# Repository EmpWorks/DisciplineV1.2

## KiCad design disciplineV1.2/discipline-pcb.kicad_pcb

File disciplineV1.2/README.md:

# DISCIPLINE V1.5
Originally created by coseyfannitutti 

**65% keyboard assembled with only through hole components, including usb type-c**

### Disclaimer
This board is a heavily-modified coseyfannitutti DISCIPLINE V1 Pcb While the schematic, basic layout etc is essentially the same, it supports additional features like Hot-swap,Encoder etc.

Key differences:
- supports hotswap PCB sockets
- added WS2812B Led strip footprint for backlit 
- Optional encoder support

Disclaimer: Use these files at your own risk.

## Assembly
For the components required, you may refer to the bill of materials here [BOM](https://octopart.com/bom-tool/W4rybyut).

All the components can be soldered using a regular soldering iron.

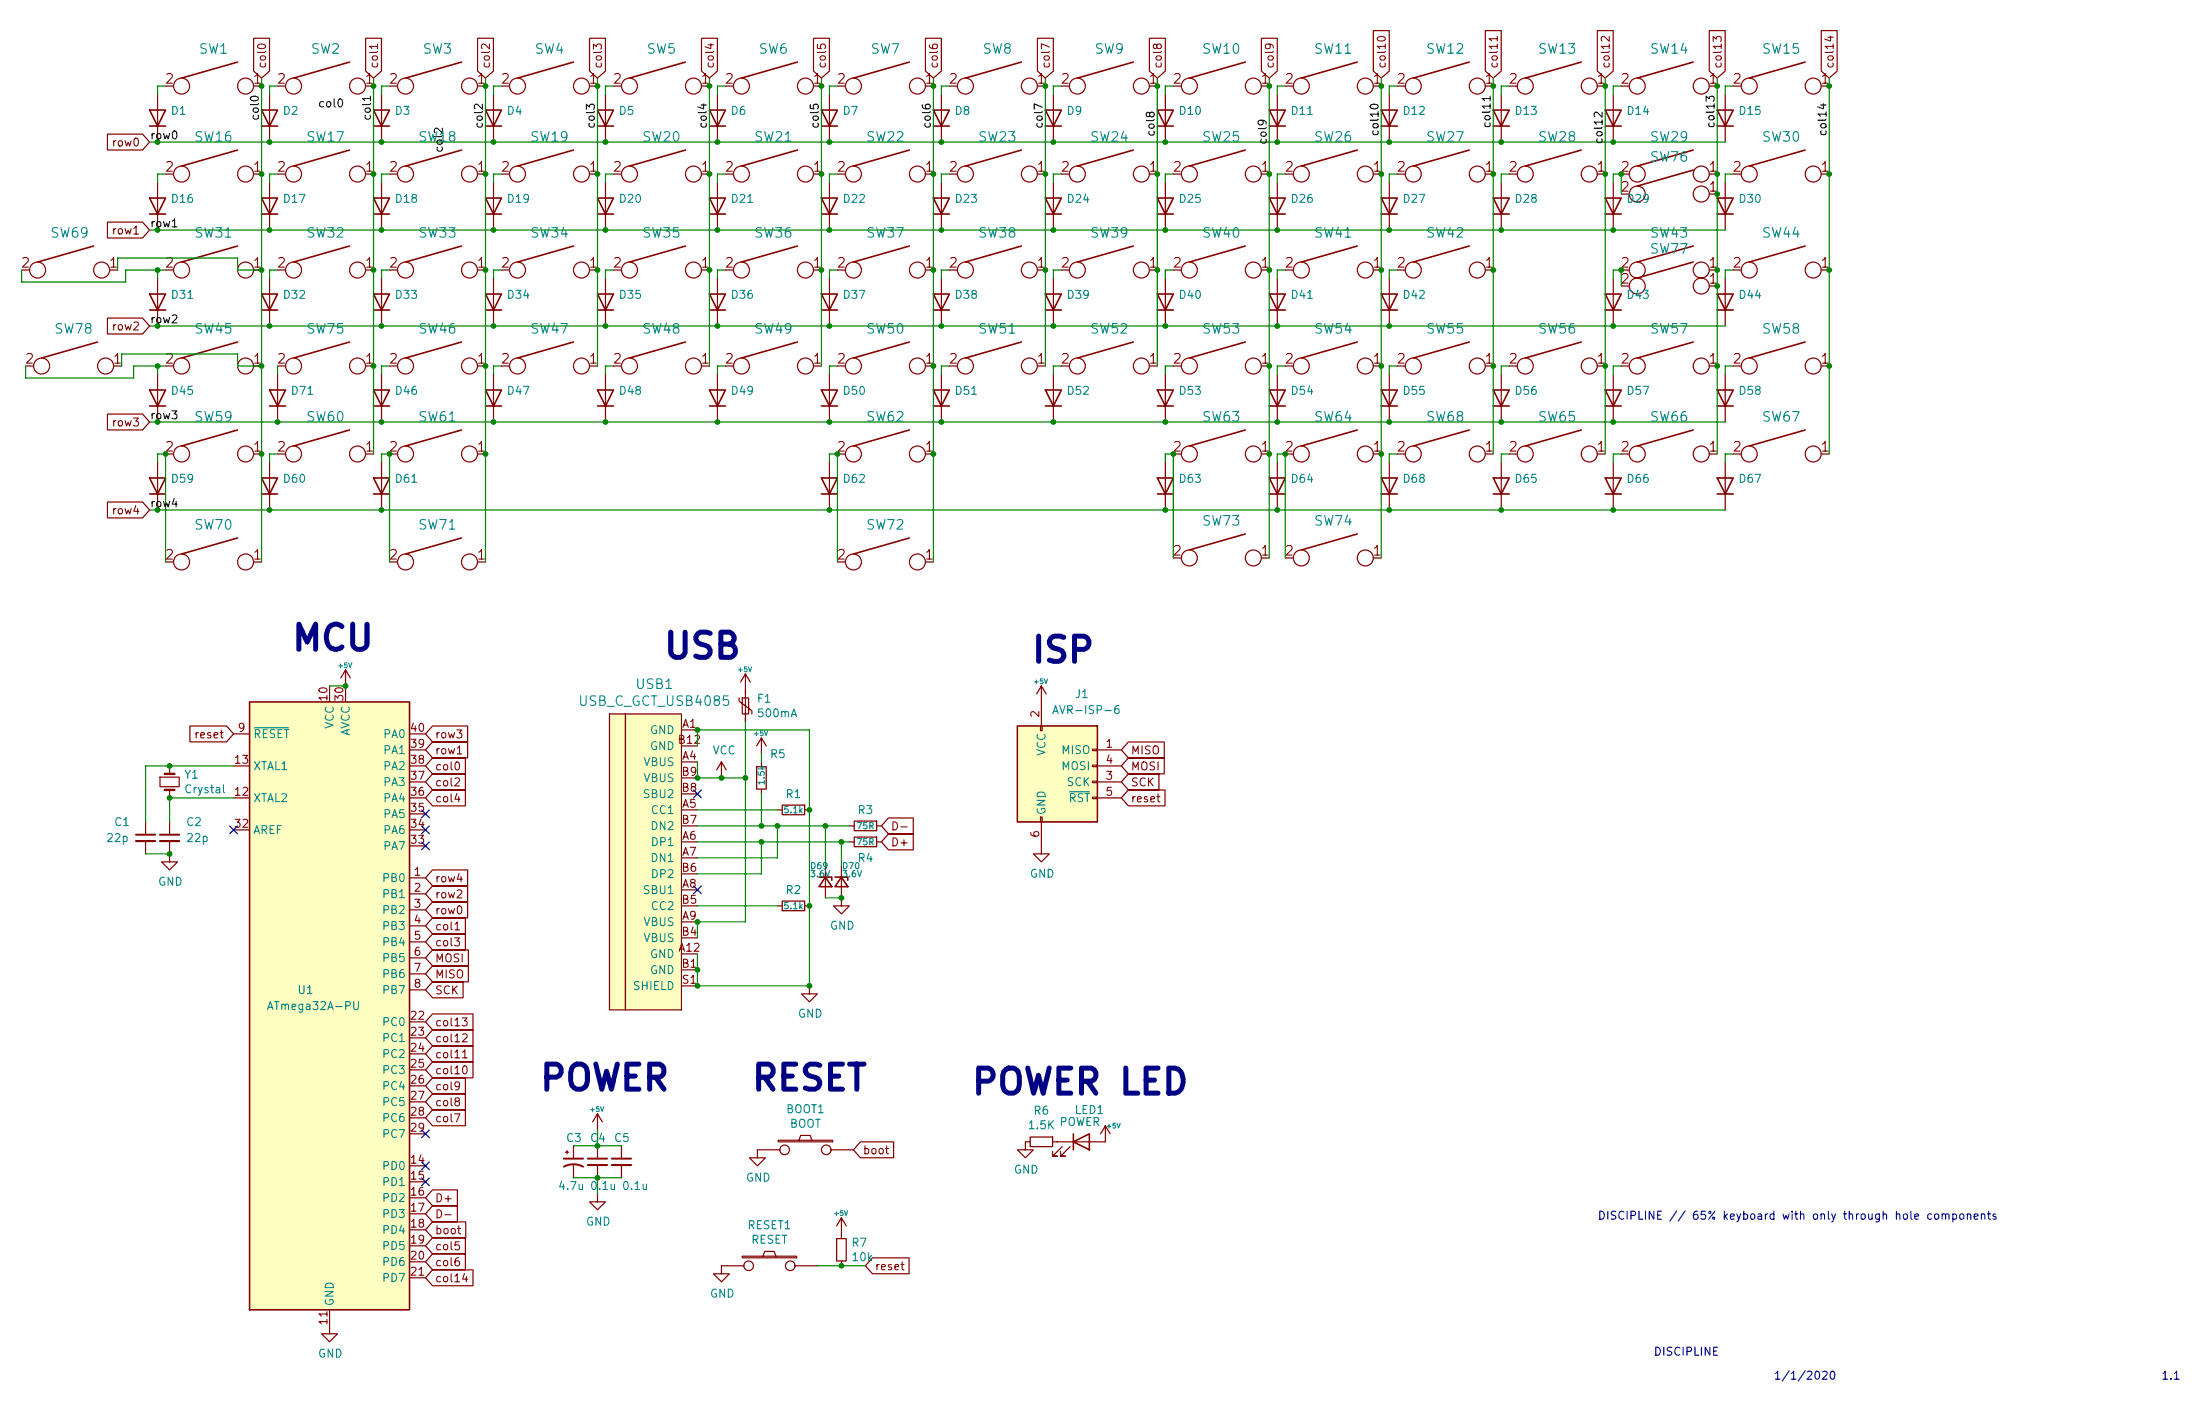
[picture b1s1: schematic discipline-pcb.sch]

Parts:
BOOT1: BOOT; SW_PUSH_6mm
C1, C2: 22p; C_Disc_D3.0mm_W1.6mm_P2.50mm
C3: 4.7u; CP_Radial_D4.0mm_P1.50mm
C4, C5: 0.1u; C_Disc_D4.3mm_W1.9mm_P5.00mm
D1, D2, D3, D4, D5, D6, D7, D8, D9, D10, D11, D12, D13, D14, D15, D16, D17, D18, D19, D20, D21, D22, D23, D24, D25, D26, D27, D28, D29, D30, D31, D32, D33, D34, D35, D36, D37, D38, D39, D40, D41, D42, D43, D44, D45, D46, D47, D48, D49, D50, D51, D52, D53, D54, D55, D56, D57, D58, D59, D60, D61, D62, D63, D64, D65, D66, D67, D68, D71: D_DO-35_SOD27_P5.08mm_Horizontal
D69, D70: 3.6V; D_DO-35_SOD27_P5.08mm_Horizontal
F1: 500mA; polyfuse_5.1mm
J1: AVR-ISP-6; AVR_ICSP_3x2
LED1: POWER; LED_D3.0mm
R1, R2: 5.1k; R_Axial_DIN0204_L3.6mm_D1.6mm_P5.08mm_Horizontal
R3, R4: 75R; R_Axial_DIN0204_L3.6mm_D1.6mm_P5.08mm_Horizontal
R5: 1.5k; R_Axial_DIN0204_L3.6mm_D1.6mm_P5.08mm_Horizontal
R6: 1.5K; R_Axial_DIN0204_L3.6mm_D1.6mm_P5.08mm_Horizontal
R7: 10k; R_Axial_DIN0204_L3.6mm_D1.6mm_P5.08mm_Horizontal
RESET1: RESET; SW_PUSH_6mm
SW1, SW2, SW3, SW4, SW5, SW6, SW7, SW8, SW9, SW10, SW11, SW12, SW13, SW15, SW17, SW18, SW19, SW20, SW21, SW22, SW23, SW24, SW25, SW26, SW27, SW28, SW30, SW32, SW33, SW34, SW35, SW36, SW37, SW38, SW39, SW40, SW41, SW42, SW44, SW46, SW47, SW48, SW49, SW50, SW51, SW52, SW53, SW54, SW55, SW57, SW58, SW62, SW65, SW66, SW67, SW68, SW72, SW75: KEYSW; MXOnly-1U-Hotswap
SW14: KEYSW; MXOnly-2U-Hotswap
SW16, SW29, SW70, SW71, SW73, SW74: KEYSW; MXOnly-1.5U-Hotswap
SW31, SW56: KEYSW; MXOnly-1.75U-Hotswap
SW43, SW45: KEYSW; MXOnly-2.25U-Hotswap
SW59, SW60, SW61, SW63, SW64, SW69: KEYSW; MXOnly-1.25U-Hotswap
SW76: KEYSW; SW_Cherry_MX1A_ISOEnter_PCB_ReversedStabilizer
SW77: KEYSW; SW_Cherry_MX1A_1.00u_PCB-NOSCREEN
SW78: KEYSW; SW_Cherry_MX1A_1.25u_PCBNOSCREEN
U1: ATmega32A-PU; DIP-40_W15.24mm
USB1: USB_C_GCT_USB4085
Y1: Crystal; Crystal_HC49-4H_Vertical

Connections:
+5V: C3.1, C4.1, C5.1, F1.1, J1.2 (VCC), LED1.2 (A), R5.1, R7.1, U1.10 (VCC), U1.30 (AVCC); also elsewhere on the board
D+: R4.1, U1.16 (PD2)
D-: R3.1, U1.17 (PD3)
GND: BOOT1.1, C1.2, C2.2, C3.2, C4.2, C5.2, D69.2 (A), D70.2 (A), J1.6 (GND), R1.1, R2.2, R6.2, RESET1.1, U1.11 (GND), U1.31 (GND), USB1.A1 (GND), USB1.A12 (GND), USB1.B1 (GND), USB1.B12 (GND), USB1.S1 (SHIELD); also elsewhere on the board
MISO: J1.1 (MISO), U1.7 (PB6)
MOSI: J1.4 (MOSI), U1.6 (PB5)
unnamed: C1.1, U1.13 (XTAL1), Y1.1
unnamed: C2.1, U1.12 (XTAL2), Y1.2
unnamed: D1.2 (A), SW1.2
unnamed: D2.2 (A), SW2.2
unnamed: D3.2 (A), SW3.2
unnamed: D4.2 (A), SW4.2
unnamed: D5.2 (A), SW5.2
unnamed: D6.2 (A), SW6.2
unnamed: D7.2 (A), SW7.2
unnamed: D8.2 (A), SW8.2
unnamed: D9.2 (A), SW9.2
unnamed: D10.2 (A), SW10.2
unnamed: D11.2 (A), SW11.2
unnamed: D12.2 (A), SW12.2
unnamed: D13.2 (A), SW13.2
unnamed: D14.2 (A), SW14.2
unnamed 22: D15.2 (A), SW15.2; also elsewhere on the board
unnamed: D16.2 (A), SW16.2
unnamed: D17.2 (A), SW17.2
unnamed: D18.2 (A), SW18.2
unnamed: D19.2 (A), SW19.2
unnamed: D20.2 (A), SW20.2
unnamed: D21.2 (A), SW21.2
unnamed: D22.2 (A), SW22.2
unnamed: D23.2 (A), SW23.2
unnamed: D24.2 (A), SW24.2
unnamed: D25.2 (A), SW25.2
unnamed: D26.2 (A), SW26.2
unnamed: D27.2 (A), SW27.2
unnamed: D28.2 (A), SW28.2
unnamed: D29.2 (A), SW29.2, SW76.2
unnamed: D30.2 (A), SW30.2
unnamed: D31.2 (A), SW31.2, SW69.2
unnamed: D32.2 (A), SW32.2
unnamed: D33.2 (A), SW33.2
unnamed: D34.2 (A), SW34.2
unnamed: D35.2 (A), SW35.2
unnamed: D36.2 (A), SW36.2
unnamed: D37.2 (A), SW37.2
unnamed: D38.2 (A), SW38.2
unnamed: D39.2 (A), SW39.2
unnamed: D40.2 (A), SW40.2
unnamed: D41.2 (A), SW41.2
unnamed: D42.2 (A), SW42.2
unnamed: D43.2 (A), SW43.2, SW77.2
unnamed: D44.2 (A), SW44.2
unnamed: D45.2 (A), SW45.2, SW78.2
unnamed: D46.2 (A), SW46.2
unnamed: D47.2 (A), SW47.2
unnamed: D48.2 (A), SW48.2
unnamed: D49.2 (A), SW49.2
unnamed: D50.2 (A), SW50.2
unnamed: D51.2 (A), SW51.2
unnamed: D52.2 (A), SW52.2
unnamed: D53.2 (A), SW53.2
unnamed: D54.2 (A), SW54.2
unnamed: D55.2 (A), SW55.2
unnamed: D56.2 (A), SW56.2
unnamed: D57.2 (A), SW57.2
unnamed: D58.2 (A), SW58.2
unnamed: D59.2 (A), SW59.2, SW70.2
unnamed: D60.2 (A), SW60.2
unnamed: D61.2 (A), SW61.2, SW71.2
unnamed: D62.2 (A), SW62.2, SW72.2
unnamed: D63.2 (A), SW63.2, SW73.2
unnamed: D64.2 (A), SW64.2, SW74.2
unnamed: D65.2 (A), SW65.2
unnamed: D66.2 (A), SW66.2
unnamed: D67.2 (A), SW67.2
unnamed: D68.2 (A), SW68.2
unnamed: D69.1 (K), R3.2, R5.2, USB1.A7 (DN1), USB1.B7 (DN2)
unnamed: D70.1 (K), R4.2, USB1.A6 (DP1), USB1.B6 (DP2)
unnamed: D71.2 (A), SW75.2
unnamed: LED1.1 (K), R6.1
unnamed: R1.2, USB1.A5 (CC1)
unnamed: R2.1, USB1.B5 (CC2)
SCK: J1.3 (SCK), U1.8 (PB7)
VCC: F1.2, USB1.A4 (VBUS), USB1.A9 (VBUS), USB1.B4 (VBUS), USB1.B9 (VBUS)
a: U1.14 (PD0); also elsewhere on the board
b: U1.15 (PD1); also elsewhere on the board
boot: BOOT1.2, U1.18 (PD4)
col0: SW1.1, SW16.1, SW31.1, SW45.1, SW59.1, SW69.1, SW70.1, SW78.1, U1.38 (PA2)
col1: SW2.1, SW17.1, SW32.1, SW60.1, SW75.1, U1.4 (PB3)
col2: SW3.1, SW18.1, SW33.1, SW46.1, SW61.1, SW71.1, U1.37 (PA3)
col3: SW4.1, SW19.1, SW34.1, SW47.1, U1.5 (PB4)
col4: SW5.1, SW20.1, SW35.1, SW48.1, U1.36 (PA4)
col5: SW6.1, SW21.1, SW36.1, SW49.1, U1.19 (PD5)
col6: SW7.1, SW22.1, SW37.1, SW50.1, SW62.1, SW72.1, U1.20 (PD6)
col7: SW8.1, SW23.1, SW38.1, SW51.1, U1.28 (PC6)
col8: SW9.1, SW24.1, SW39.1, SW52.1, U1.27 (PC5)
col9: SW10.1, SW25.1, SW40.1, SW53.1, SW63.1, SW73.1, U1.26 (PC4)
col10: SW11.1, SW26.1, SW41.1, SW54.1, SW64.1, SW74.1, U1.25 (PC3)
col11: SW12.1, SW27.1, SW42.1, SW55.1, SW68.1, U1.24 (PC2)
col12: SW13.1, SW28.1, SW56.1, SW65.1, U1.23 (PC1)
col13: SW14.1, SW29.1, SW43.1, SW57.1, SW66.1, SW76.1, SW77.1, U1.22 (PC0)
col14: SW15.1, SW30.1, SW44.1, SW58.1, SW67.1, U1.21 (PD7); also elsewhere on the board
led: U1.29 (PC7); also elsewhere on the board
reset: J1.5 (~RST), R7.2, RESET1.2, U1.9 (~RESET)
row0: D1.1 (K), D2.1 (K), D3.1 (K), D4.1 (K), D5.1 (K), D6.1 (K), D7.1 (K), D8.1 (K), D9.1 (K), D10.1 (K), D11.1 (K), D12.1 (K), D13.1 (K), D14.1 (K), D15.1 (K), U1.3 (PB2)
row1: D16.1 (K), D17.1 (K), D18.1 (K), D19.1 (K), D20.1 (K), D21.1 (K), D22.1 (K), D23.1 (K), D24.1 (K), D25.1 (K), D26.1 (K), D27.1 (K), D28.1 (K), D29.1 (K), D30.1 (K), U1.39 (PA1)
row2: D31.1 (K), D32.1 (K), D33.1 (K), D34.1 (K), D35.1 (K), D36.1 (K), D37.1 (K), D38.1 (K), D39.1 (K), D40.1 (K), D41.1 (K), D42.1 (K), D43.1 (K), D44.1 (K), U1.2 (PB1)
row3: D45.1 (K), D46.1 (K), D47.1 (K), D48.1 (K), D49.1 (K), D50.1 (K), D51.1 (K), D52.1 (K), D53.1 (K), D54.1 (K), D55.1 (K), D56.1 (K), D57.1 (K), D58.1 (K), D71.1 (K), U1.40 (PA0)
row4: D59.1 (K), D60.1 (K), D61.1 (K), D62.1 (K), D63.1 (K), D64.1 (K), D65.1 (K), D66.1 (K), D67.1 (K), D68.1 (K), U1.1 (PB0)

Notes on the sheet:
DISCIPLINE // 65% keyboard with only through hole components
1/1/2020
DISCIPLINE
1.1
MCU
USB
ISP
POWER
RESET
POWER LED

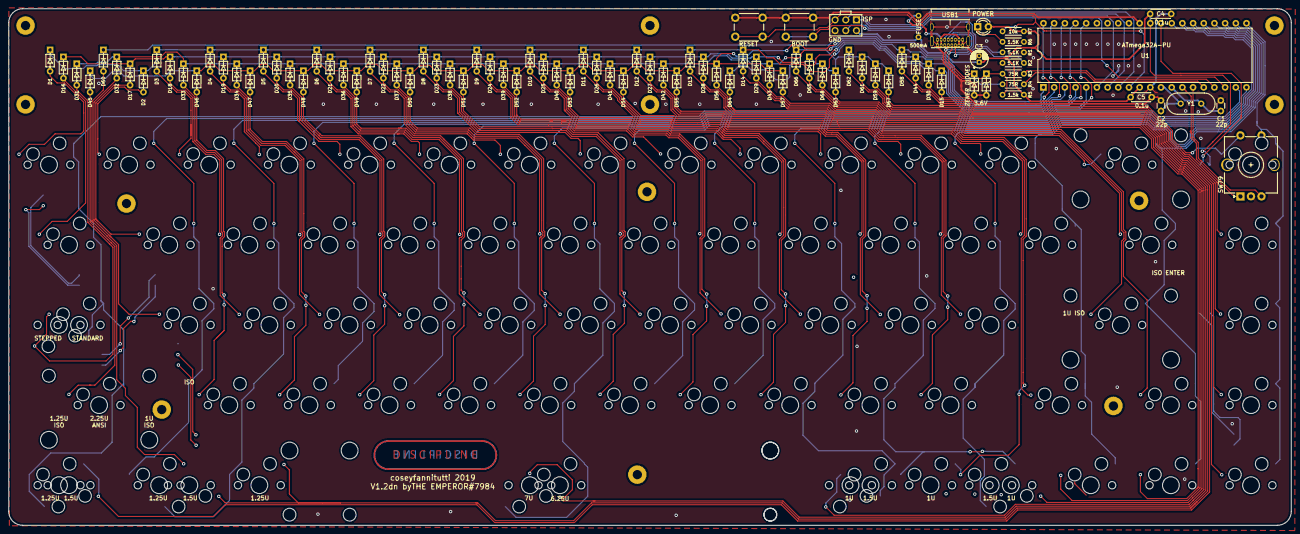
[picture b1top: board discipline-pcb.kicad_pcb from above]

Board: 2 copper layers, 304.9 x 122.8 mm, 176 parts (0 on the bottom side), 108 nets.

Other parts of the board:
J2, J2#2, J2#3, J2#4, J2#5, J2#6, J2#7, J2#8, J2#9, J2#10: Conn_01x03_Male; StripLED
ST72: 7U; MX-7U-Stabilizer
SW79: Rotary_Encoder_Switch; RotaryEncoder_Alps_EC12E-Switch_Vertical_H20mm

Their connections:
+5V: J2.3, J2#2.3, J2#3.3, J2#4.3, J2#5.3, J2#6.3, J2#7.3, J2#8.3, J2#9.3, J2#10.3; also elsewhere on the board
GND: J2.1, J2#2.1, J2#3.1, J2#4.1, J2#5.1, J2#6.1, J2#7.1, J2#8.1, J2#9.1, J2#10.1, SW79.C; also elsewhere on the board
unnamed 22: SW79.S1; also elsewhere on the board
a: SW79.A; also elsewhere on the board
b: SW79.B; also elsewhere on the board
col14: SW79.S2; also elsewhere on the board
led: J2.2, J2#2.2, J2#3.2, J2#4.2, J2#5.2, J2#6.2, J2#7.2, J2#8.2, J2#9.2, J2#10.2; also elsewhere on the board

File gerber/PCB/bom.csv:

Designator,Footprint,Quantity,Value,LCSC Part #
SW1,MXOnly-1U-Hotswap,1,KEYSW,
SW2,MXOnly-1U-Hotswap,1,KEYSW,
SW3,MXOnly-1U-Hotswap,1,KEYSW,
SW4,MXOnly-1U-Hotswap,1,KEYSW,
SW5,MXOnly-1U-Hotswap,1,KEYSW,
SW6,MXOnly-1U-Hotswap,1,KEYSW,
SW7,MXOnly-1U-Hotswap,1,KEYSW,
SW8,MXOnly-1U-Hotswap,1,KEYSW,
SW9,MXOnly-1U-Hotswap,1,KEYSW,
SW10,MXOnly-1U-Hotswap,1,KEYSW,
SW11,MXOnly-1U-Hotswap,1,KEYSW,
SW12,MXOnly-1U-Hotswap,1,KEYSW,
SW13,MXOnly-1U-Hotswap,1,KEYSW,
SW15,MXOnly-1U-Hotswap,1,KEYSW,
SW17,MXOnly-1U-Hotswap,1,KEYSW,
SW18,MXOnly-1U-Hotswap,1,KEYSW,
SW19,MXOnly-1U-Hotswap,1,KEYSW,
SW20,MXOnly-1U-Hotswap,1,KEYSW,
SW21,MXOnly-1U-Hotswap,1,KEYSW,
SW22,MXOnly-1U-Hotswap,1,KEYSW,
SW23,MXOnly-1U-Hotswap,1,KEYSW,
SW24,MXOnly-1U-Hotswap,1,KEYSW,
SW25,MXOnly-1U-Hotswap,1,KEYSW,
SW26,MXOnly-1U-Hotswap,1,KEYSW,
SW27,MXOnly-1U-Hotswap,1,KEYSW,
SW28,MXOnly-1U-Hotswap,1,KEYSW,
SW30,MXOnly-1U-Hotswap,1,KEYSW,
SW32,MXOnly-1U-Hotswap,1,KEYSW,
SW33,MXOnly-1U-Hotswap,1,KEYSW,
SW34,MXOnly-1U-Hotswap,1,KEYSW,
SW35,MXOnly-1U-Hotswap,1,KEYSW,
SW36,MXOnly-1U-Hotswap,1,KEYSW,
SW37,MXOnly-1U-Hotswap,1,KEYSW,
SW38,MXOnly-1U-Hotswap,1,KEYSW,
SW39,MXOnly-1U-Hotswap,1,KEYSW,
SW40,MXOnly-1U-Hotswap,1,KEYSW,
SW41,MXOnly-1U-Hotswap,1,KEYSW,
SW42,MXOnly-1U-Hotswap,1,KEYSW,
SW44,MXOnly-1U-Hotswap,1,KEYSW,
SW46,MXOnly-1U-Hotswap,1,KEYSW,
SW47,MXOnly-1U-Hotswap,1,KEYSW,
SW48,MXOnly-1U-Hotswap,1,KEYSW,
SW49,MXOnly-1U-Hotswap,1,KEYSW,
SW50,MXOnly-1U-Hotswap,1,KEYSW,
SW51,MXOnly-1U-Hotswap,1,KEYSW,
SW52,MXOnly-1U-Hotswap,1,KEYSW,
SW53,MXOnly-1U-Hotswap,1,KEYSW,
SW54,MXOnly-1U-Hotswap,1,KEYSW,
SW55,MXOnly-1U-Hotswap,1,KEYSW,
SW57,MXOnly-1U-Hotswap,1,KEYSW,
SW58,MXOnly-1U-Hotswap,1,KEYSW,
SW62,MXOnly-1U-Hotswap,1,KEYSW,
SW65,MXOnly-1U-Hotswap,1,KEYSW,
SW66,MXOnly-1U-Hotswap,1,KEYSW,
SW67,MXOnly-1U-Hotswap,1,KEYSW,
SW14,MXOnly-2U-Hotswap,1,KEYSW,
SW29,MXOnly-1.5U-Hotswap,1,KEYSW,
SW31,MXOnly-1.75U-Hotswap,1,KEYSW,
SW43,MXOnly-2.25U-Hotswap,1,KEYSW,
SW45,MXOnly-2.25U-Hotswap,1,KEYSW,
SW56,MXOnly-1.75U-Hotswap,1,KEYSW,
SW59,MXOnly-1.25U-Hotswap,1,KEYSW,
SW60,MXOnly-1.25U-Hotswap,1,KEYSW,
SW61,MXOnly-1.25U-Hotswap,1,KEYSW,
ST72,MX-7U-Stabilizer,1,7U,
SW68,MXOnly-1U-Hotswap,1,KEYSW,
D1,D_DO-35_SOD27_P5.08mm_Horizontal,1, ,
D2,D_DO-35_SOD27_P5.08mm_Horizontal,1, ,
D3,D_DO-35_SOD27_P5.08mm_Horizontal,1, ,
D4,D_DO-35_SOD27_P5.08mm_Horizontal,1, ,
D5,D_DO-35_SOD27_P5.08mm_Horizontal,1, ,
D6,D_DO-35_SOD27_P5.08mm_Horizontal,1, ,
D7,D_DO-35_SOD27_P5.08mm_Horizontal,1, ,
D8,D_DO-35_SOD27_P5.08mm_Horizontal,1, ,
D9,D_DO-35_SOD27_P5.08mm_Horizontal,1, ,
D10,D_DO-35_SOD27_P5.08mm_Horizontal,1, ,
D11,D_DO-35_SOD27_P5.08mm_Horizontal,1, ,
D12,D_DO-35_SOD27_P5.08mm_Horizontal,1, ,
D13,D_DO-35_SOD27_P5.08mm_Horizontal,1, ,
D14,D_DO-35_SOD27_P5.08mm_Horizontal,1, ,
D15,D_DO-35_SOD27_P5.08mm_Horizontal,1, ,
D16,D_DO-35_SOD27_P5.08mm_Horizontal,1, ,
D17,D_DO-35_SOD27_P5.08mm_Horizontal,1, ,
D18,D_DO-35_SOD27_P5.08mm_Horizontal,1, ,
D19,D_DO-35_SOD27_P5.08mm_Horizontal,1, ,
D20,D_DO-35_SOD27_P5.08mm_Horizontal,1, ,
D21,D_DO-35_SOD27_P5.08mm_Horizontal,1, ,
D22,D_DO-35_SOD27_P5.08mm_Horizontal,1, ,
D23,D_DO-35_SOD27_P5.08mm_Horizontal,1, ,
D24,D_DO-35_SOD27_P5.08mm_Horizontal,1, ,
D25,D_DO-35_SOD27_P5.08mm_Horizontal,1, ,
D26,D_DO-35_SOD27_P5.08mm_Horizontal,1, ,
D27,D_DO-35_SOD27_P5.08mm_Horizontal,1, ,
D28,D_DO-35_SOD27_P5.08mm_Horizontal,1, ,
D29,D_DO-35_SOD27_P5.08mm_Horizontal,1, ,
D30,D_DO-35_SOD27_P5.08mm_Horizontal,1, ,
D31,D_DO-35_SOD27_P5.08mm_Horizontal,1, ,
D32,D_DO-35_SOD27_P5.08mm_Horizontal,1, ,
D33,D_DO-35_SOD27_P5.08mm_Horizontal,1, ,
D34,D_DO-35_SOD27_P5.08mm_Horizontal,1, ,
D35,D_DO-35_SOD27_P5.08mm_Horizontal,1, ,
D36,D_DO-35_SOD27_P5.08mm_Horizontal,1, ,
D37,D_DO-35_SOD27_P5.08mm_Horizontal,1, ,
D38,D_DO-35_SOD27_P5.08mm_Horizontal,1, ,
D39,D_DO-35_SOD27_P5.08mm_Horizontal,1, ,
D40,D_DO-35_SOD27_P5.08mm_Horizontal,1, ,
D41,D_DO-35_SOD27_P5.08mm_Horizontal,1, ,
D42,D_DO-35_SOD27_P5.08mm_Horizontal,1, ,
D43,D_DO-35_SOD27_P5.08mm_Horizontal,1, ,
D44,D_DO-35_SOD27_P5.08mm_Horizontal,1, ,
D45,D_DO-35_SOD27_P5.08mm_Horizontal,1, ,
D46,D_DO-35_SOD27_P5.08mm_Horizontal,1, ,
D47,D_DO-35_SOD27_P5.08mm_Horizontal,1, ,
D48,D_DO-35_SOD27_P5.08mm_Horizontal,1, ,
D49,D_DO-35_SOD27_P5.08mm_Horizontal,1, ,
D50,D_DO-35_SOD27_P5.08mm_Horizontal,1, ,
D51,D_DO-35_SOD27_P5.08mm_Horizontal,1, ,
D52,D_DO-35_SOD27_P5.08mm_Horizontal,1, ,
D53,D_DO-35_SOD27_P5.08mm_Horizontal,1, ,
D54,D_DO-35_SOD27_P5.08mm_Horizontal,1, ,
D55,D_DO-35_SOD27_P5.08mm_Horizontal,1, ,
D56,D_DO-35_SOD27_P5.08mm_Horizontal,1, ,
D57,D_DO-35_SOD27_P5.08mm_Horizontal,1, ,
D58,D_DO-35_SOD27_P5.08mm_Horizontal,1, ,
D59,D_DO-35_SOD27_P5.08mm_Horizontal,1, ,
D60,D_DO-35_SOD27_P5.08mm_Horizontal,1, ,
D61,D_DO-35_SOD27_P5.08mm_Horizontal,1, ,
D62,D_DO-35_SOD27_P5.08mm_Horizontal,1, ,
D63,D_DO-35_SOD27_P5.08mm_Horizontal,1, ,
D64,D_DO-35_SOD27_P5.08mm_Horizontal,1, ,
D65,D_DO-35_SOD27_P5.08mm_Horizontal,1, ,
D66,D_DO-35_SOD27_P5.08mm_Horizontal,1, ,
D67,D_DO-35_SOD27_P5.08mm_Horizontal,1, ,
D68,D_DO-35_SOD27_P5.08mm_Horizontal,1, ,
R3,R_Axial_DIN0204_L3.6mm_D1.6mm_P7.62mm_Horizontal,1,75R,
R4,R_Axial_DIN0204_L3.6mm_D1.6mm_P7.62mm_Horizontal,1,75R,
R1,R_Axial_DIN0204_L3.6mm_D1.6mm_P7.62mm_Horizontal,1,5.1k,
RESET1,SW_PUSH_6mm,1,RESET,
LED1,LED_D3.0mm,1,POWER,
R6,R_Axial_DIN0204_L3.6mm_D1.6mm_P7.62mm_Horizontal,1,1.5K,
BOOT1,SW_PUSH_6mm,1,BOOT,
F1,polyfuse_5.1mm,1,500mA,
C3,CP_Radial_D4.0mm_P1.50mm,1,4.7u,
C4,C_Disc_D4.3mm_W1.9mm_P5.00mm,1,0.1u,
C5,C_Disc_D4.3mm_W1.9mm_P5.00mm,1,0.1u,
SW63,MXOnly-1.25U-Hotswap,1,KEYSW,
SW64,MXOnly-1.25U-Hotswap,1,KEYSW,
USB1,USB_C_GCT_USB4085,1,USB_C_GCT_USB4085,
C1,C_Disc_D3.0mm_W1.6mm_P2.50mm,1,22p,
C2,C_Disc_D3.0mm_W1.6mm_P2.50mm,1,22p,
D69,D_DO-35_SOD27_P5.08mm_Horizontal,1,3.6V,
D70,D_DO-35_SOD27_P5.08mm_Horizontal,1,3.6V,
R5,R_Axial_DIN0204_L3.6mm_D1.6mm_P7.62mm_Horizontal,1,1.5k,
Y1,Crystal_HC49-4H_Vertical,1,Crystal,
R7,R_Axial_DIN0204_L3.6mm_D1.6mm_P7.62mm_Horizontal,1,10k,
R2,R_Axial_DIN0204_L3.6mm_D1.6mm_P7.62mm_Horizontal,1,5.1k,
J1,AVR_ICSP_3x2,1,AVR-ISP-6,
SW69,MXOnly-1.25U-Hotswap,1,KEYSW,
SW70,MXOnly-1.5U-Hotswap,1,KEYSW,
SW71,MXOnly-1.5U-Hotswap,1,KEYSW,
SW72,MXOnly-1U-Hotswap,1,KEYSW,
SW73,MXOnly-1.5U-Hotswap,1,KEYSW,
SW74,MXOnly-1.5U-Hotswap,1,KEYSW,
SW16,MXOnly-1.5U-Hotswap,1,KEYSW,
U1,DIP-40_W15.24mm,1,ATmega32A-PU,
J2_10,StripLED,1,Conn_01x03_Male,
SW79,RotaryEncoder_Alps_EC12E-Switch_Vertical_H20mm,1,Rotary_Encoder_Switch,
J2_9,StripLED,1,Conn_01x03_Male,
J2_8,StripLED,1,Conn_01x03_Male,
J2_7,StripLED,1,Conn_01x03_Male,
J2_6,StripLED,1,Conn_01x03_Male,
J2_5,StripLED,1,Conn_01x03_Male,
J2_4,StripLED,1,Conn_01x03_Male,
J2_3,StripLED,1,Conn_01x03_Male,
J2_2,StripLED,1,Conn_01x03_Male,
J2,StripLED,1,Conn_01x03_Male,
